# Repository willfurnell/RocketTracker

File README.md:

# RocketTracker
A rocket tracking and launching board for Harwell Rocket Club

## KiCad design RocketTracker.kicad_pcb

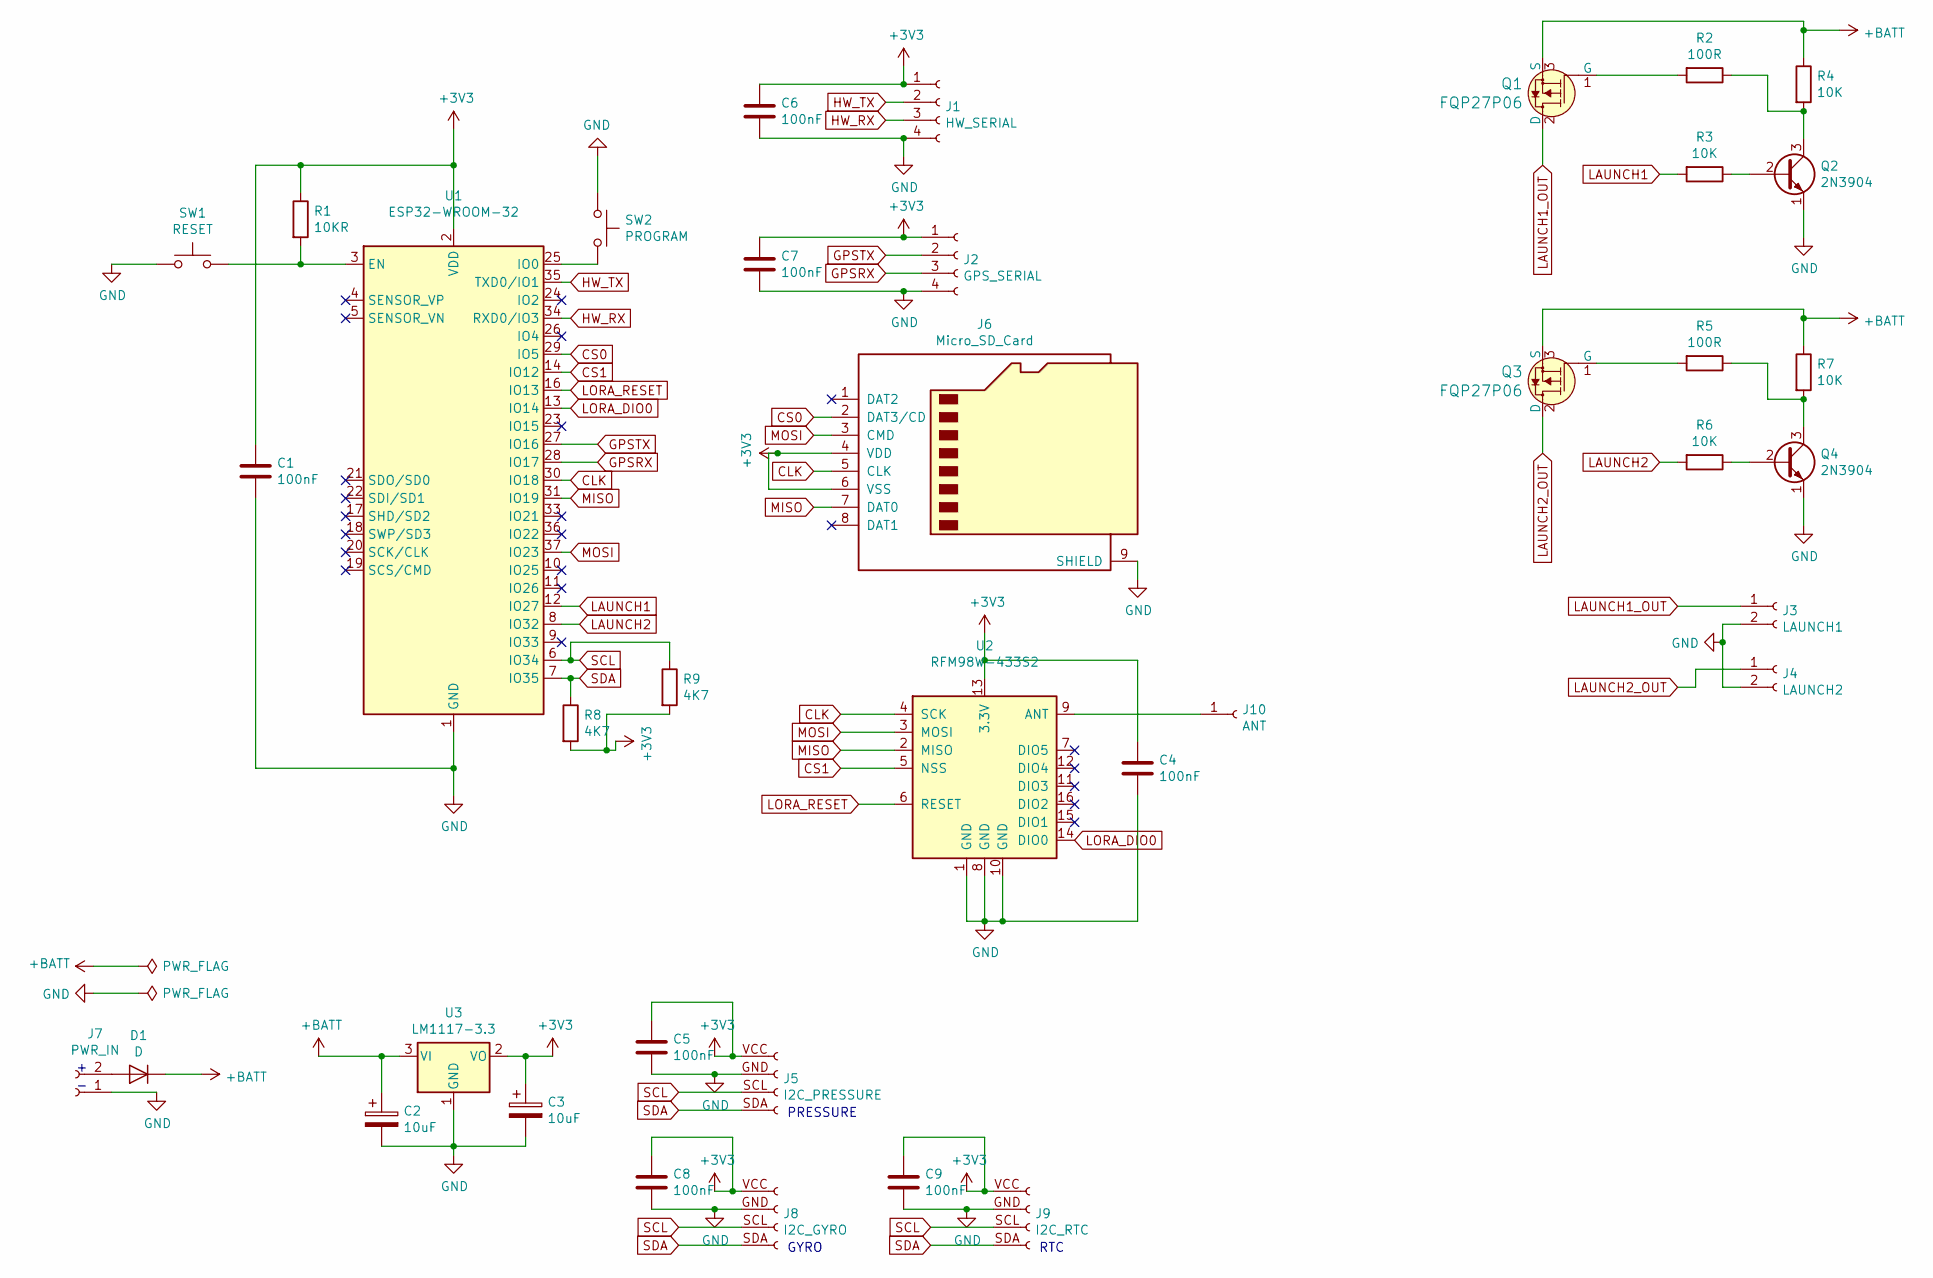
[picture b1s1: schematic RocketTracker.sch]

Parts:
C1, C4, C5, C6, C7, C8, C9: 100nF; C_0805_2012Metric_Pad1.15x1.40mm_HandSolder
C2, C3: 10uF; CP_Radial_D5.0mm_P2.50mm
D1: D; D_T-1_P5.08mm_Horizontal
J1: HW_SERIAL; PinSocket_1x04_P2.54mm_Vertical
J2: GPS_SERIAL; PinSocket_1x04_P2.54mm_Vertical
J3: LAUNCH1; SolderWirePad_1x02_P3.81mm_Drill1mm
J4: LAUNCH2; SolderWirePad_1x02_P3.81mm_Drill1mm
J5: I2C_PRESSURE; PinSocket_1x04_P2.54mm_Vertical
J6: Micro_SD_Card; microSD_HC_Molex_104031-0811
J7: PWR_IN; SolderWirePad_1x02_P3.81mm_Drill1mm
J8: I2C_GYRO; PinSocket_1x04_P2.54mm_Vertical
J9: I2C_RTC; PinSocket_1x04_P2.54mm_Vertical
J10: ANT; PinSocket_1x01_P2.54mm_Vertical
Q1, Q3: FQP27P06; TO-220-3; MPN FQP27P06; Digi-Key_PN FQP27P06-ND
Q2, Q4: 2N3904; TO-92_Inline
R1: 10KR; R_0805_2012Metric_Pad1.15x1.40mm_HandSolder
R2, R5: 100R; R_0805_2012Metric_Pad1.15x1.40mm_HandSolder
R3, R4, R6, R7: 10K; R_0805_2012Metric_Pad1.15x1.40mm_HandSolder
R8, R9: 4K7; R_0805_2012Metric_Pad1.15x1.40mm_HandSolder
SW1: RESET; FSM4JRT
SW2: PROGRAM; FSM4JRT
U1: ESP32-WROOM-32
U2: RFM98W-433S2; HOPERF_RFM69HW
U3: LM1117-3.3; TO254P470X1028X1955-3P

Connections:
+3V3: C1.1, C3.1, C4.1, C5.1, C6.1, C7.1, C8.1, C9.1, J1.1, J2.1, J5.VCC (Pin_1), J6.4 (VDD), J6.6 (VSS), J8.VCC (Pin_1), J9.VCC (Pin_1), R1.1, R8.2, R9.2, U1.2 (VDD), U2.13 (3.3V), U3.2 (VO)
+BATT: C2.1, D1.1 (K), Q1.3 (S), Q3.3 (S), R4.1, R7.1, U3.3 (VI)
CLK: J6.5 (CLK), U1.30 (IO18), U2.4 (SCK)
CS0: J6.2 (DAT3/CD), U1.29 (IO5)
CS1: U1.14 (IO12), U2.5 (NSS)
GND: C1.2, C2.2, C3.2, C4.2, C5.2, C6.2, C7.2, C8.2, C9.2, J1.4, J2.4, J3.2, J4.2, J5.GND (Pin_2), J6.9 (SHIELD), J7.1, J8.GND (Pin_2), J9.GND (Pin_2), Q2.1 (E), Q4.1 (E), SW1.1, SW2.1, U1.1 (GND), U1.15 (GND), U1.38 (GND), U1.39 (GND), U2.1 (GND), U2.8 (GND), U2.10 (GND), U3.1 (GND)
GPSRX: J2.3, U1.28 (IO17)
GPSTX: J2.2, U1.27 (IO16)
HW_RX: J1.3, U1.34 (RXD0/IO3)
HW_TX: J1.2, U1.35 (TXD0/IO1)
LAUNCH1: R3.2, U1.12 (IO27)
LAUNCH1_OUT: J3.1, Q1.2 (D)
LAUNCH2: R6.2, U1.8 (IO32)
LAUNCH2_OUT: J4.1, Q3.2 (D)
LORA_DIO0: U1.13 (IO14), U2.14 (DIO0)
LORA_RESET: U1.16 (IO13), U2.6 (RESET)
MISO: J6.7 (DAT0), U1.31 (IO19), U2.2 (MISO)
MOSI: J6.3 (CMD), U1.37 (IO23), U2.3 (MOSI)
unnamed: D1.2 (A), J7.2
unnamed: J10.1, U2.9 (ANT)
unnamed: Q1.1 (G), R2.2
unnamed: Q2.2 (B), R3.1
unnamed: Q2.3 (C), R2.1, R4.2
unnamed: Q3.1 (G), R5.2
unnamed: Q4.2 (B), R6.1
unnamed: Q4.3 (C), R5.1, R7.2
unnamed: R1.2, SW1.2, U1.3 (EN)
unnamed: SW2.2, U1.25 (IO0)
SCL: J5.SCL (Pin_3), J8.SCL (Pin_3), J9.SCL (Pin_3), R9.1, U1.6 (IO34)
SDA: J5.SDA (Pin_4), J8.SDA (Pin_4), J9.SDA (Pin_4), R8.1, U1.7 (IO35)

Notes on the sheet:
PRESSURE
GYRO
RTC

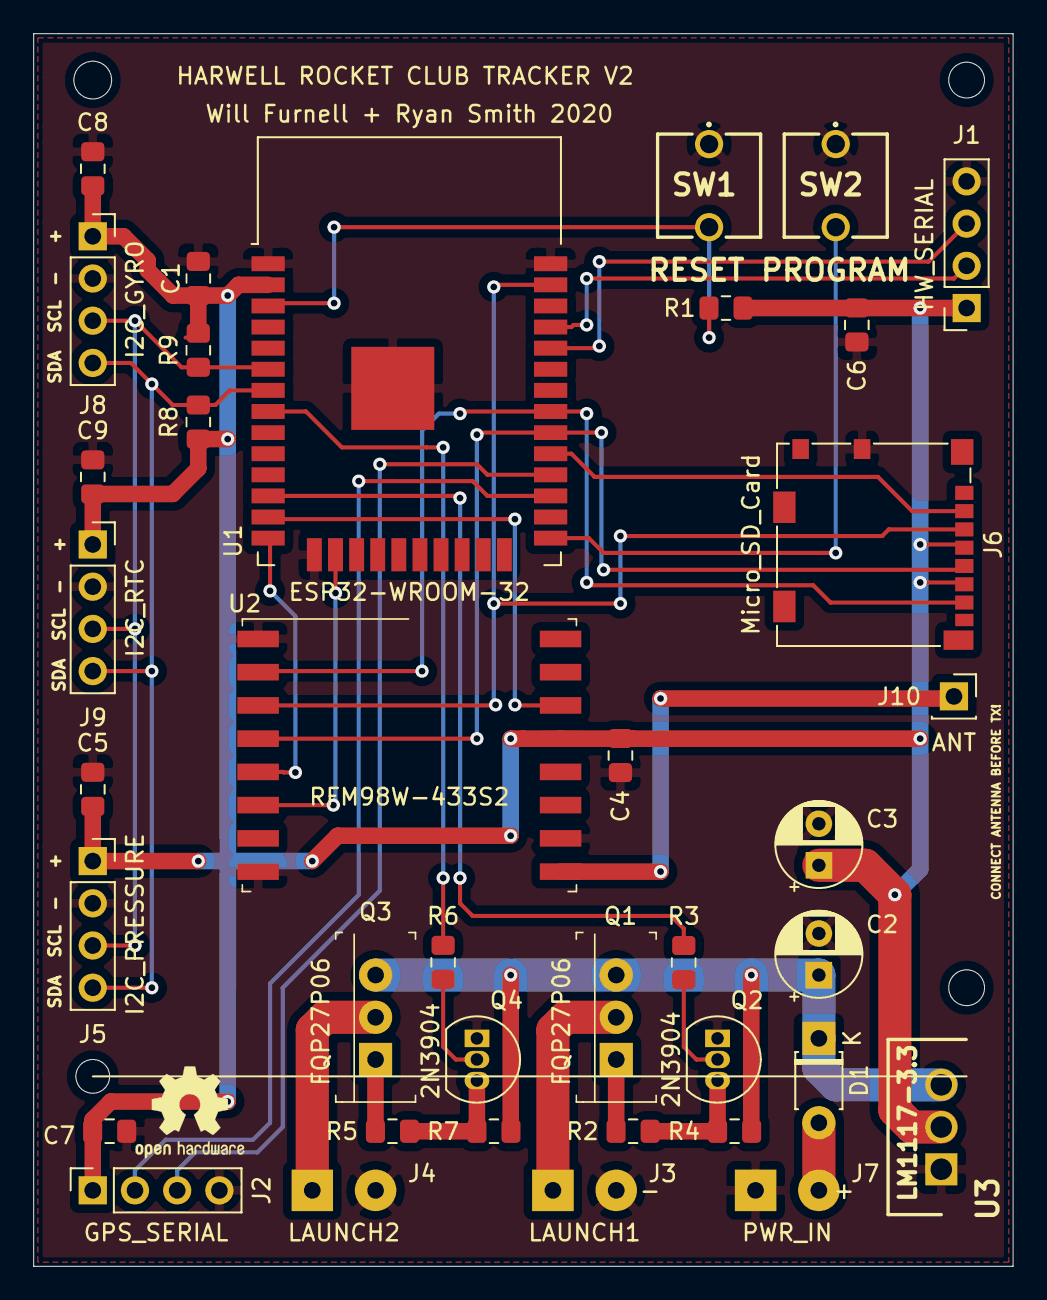
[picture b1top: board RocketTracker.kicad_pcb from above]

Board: 2 copper layers, 58.9 x 74.2 mm, 38 parts (0 on the bottom side), 30 nets.

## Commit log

2020-04-22 Add gitignore
2020-04-22 Remove files we should ignore from git
2020-04-28 Update PCB
2020-04-29 Use smaller components
2020-04-29 Connect up traces
2020-05-07 Add updated board
2020-06-17 Edited the PCB design
